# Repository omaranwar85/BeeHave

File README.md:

# BeeHave

This repository contains the board and schematic files (designed in Eagle) for the beehive monitoring system, BeeDAS (Design and development of low-power, long-range data acquisition system for beehives). It also contains a python file 'Script.py' and a numpy file containing the dataset with 1,250 days of beehive sensor data and waether recordings. The sample python script reads the numpy file and uses random forest to estimate the daily weight variations. Following packages are required to run the script.

python                    3.7.11  

pandas                    1.3.2 

matplotlib                3.4.2 

numpy                     1.18.5   

scikit-learn              0.24.2  

seaborn                   0.11.2 

The AllFeatures_shuffled_144.npy file can be downloaded using the folowing link, and should be placed in the same folder as Script.py
https://media.githubusercontent.com/media/omaranwar85/BeeHave/main/AllFeatures_shuffled_144.npy

The datasheets of used components are available online, and can be accessed using the following links

CCS811 Gas Sensor
https://www.sciosense.com/wp-content/uploads/2020/01/SC-001232-DS-2-CCS811B-Datasheet-Revision-2.pdf

SanDisk Industrial
https://images-na.ssl-images-amazon.com/images/I/91tTtUMDM3L.pdf

MMA8452Q Accelerometer
https://www.nxp.com/docs/en/data-sheet/MMA8452Q.pdf

MKR NB-1500 Board
https://store-usa.arduino.cc/products/arduino-mkr-nb-1500

HX711 Load Amplifier
https://datasheetspdf.com/pdf/842201/Aviasemiconductor/HX711/1

BME280 Sensor
https://datasheetspdf.com/pdf/1096951/Bosch/BME280/1

ADMP401 MEMS microphone
https://www.analog.com/media/en/technical-documentation/obsolete-data-sheets/ADMP401.pdf

REF3433 Voltage Reference
https://www.ti.com/lit/ds/symlink/ref3433.pdf

Sparkfun Redboard Turbo
https://www.sparkfun.com/products/14812

As this project progresses, we will be adding more to this repository.

==========================================================================

One of our accepted works at AAAI22 workshop for 'Practical deep-learning in the Wild' also uses the data collected using this system, with a significant overlap with the dataset shared in this repository. You can access this paper using the following link
https://www.researchgate.net/publication/358954859_WE-Bee_Weight_Estimator_for_Beehives_Using_Deep_Learning

If you use this dataset, please refer one of our works.

@inproceedings{anwar2022we,
  title={WE-Bee: Weight Estimator for Beehives Using Deep Learning},
  author={Anwar, Omar and Keating, Adrian and Cardell-Oliver, Rachel and Datta, Amitava and Putrino, Gino},
  booktitle={AAAI Conference on Artificial Intelligence 2022: 1st International Workshop on Practical Deep Learning in the Wild},
  year={2022}
}

@article{anwar2022BeeDAS,
title = {Design and development of low-power, long-range data acquisition system for beehives - BeeDAS},
journal = {Computers and Electronics in Agriculture},
volume = {201},
pages = {107281},
year = {2022},
issn = {0168-1699},
doi = {https://doi.org/10.1016/j.compag.2022.107281},
url = {https://www.sciencedirect.com/science/article/pii/S0168169922005932},
author = {Omar Anwar and Adrian Keating and Rachel Cardell-Oliver and Amitava Datta and Gino Putrino},
keywords = {Data acquisition, Low-power, Long-range, Beehive monitoring, Weight estimation, Random forest},
abstract = {Decision making capability of a system is highly dependent upon the quality and quantity of training data. Majority of beehive monitoring systems developed for research purposes are designed to collect data through a small set of sensors, and from locations with little geographic diversity. This hinders the development of a dataset that can be used to effectively train machine learning models. In this work, we explain the design and development of a multi-sensory, remote data acquisition system for beehives (BeeDAS), with focus on low-power consumption and long-range communication. We address design challenges associated with such systems and highlight the critical issues that need consideration. The proposed system enables collection of data from beehives at remote locations and harsh environment. Results of field deployments elucidate the effectiveness of various sensors which measure temperature, humidity, atmospheric pressure, CO2, acoustics, vibrations and the weight of a hive in hostile environment. This work also uses random forest regression to evaluate the feature importance of different sensors, environmental variables such as temperature, humidity, rain, wind speed as well as the information related to seasons, towards estimating the daily hive weight change, on a dataset comprised of 1,250 days of sensor recordings. We also evaluate the protocol designed for communication using Narrow Band Internet of Things (NB-IoT). The issues related to power optimization, sleep intervals and data storage in remote monitoring are also discussed.}
}

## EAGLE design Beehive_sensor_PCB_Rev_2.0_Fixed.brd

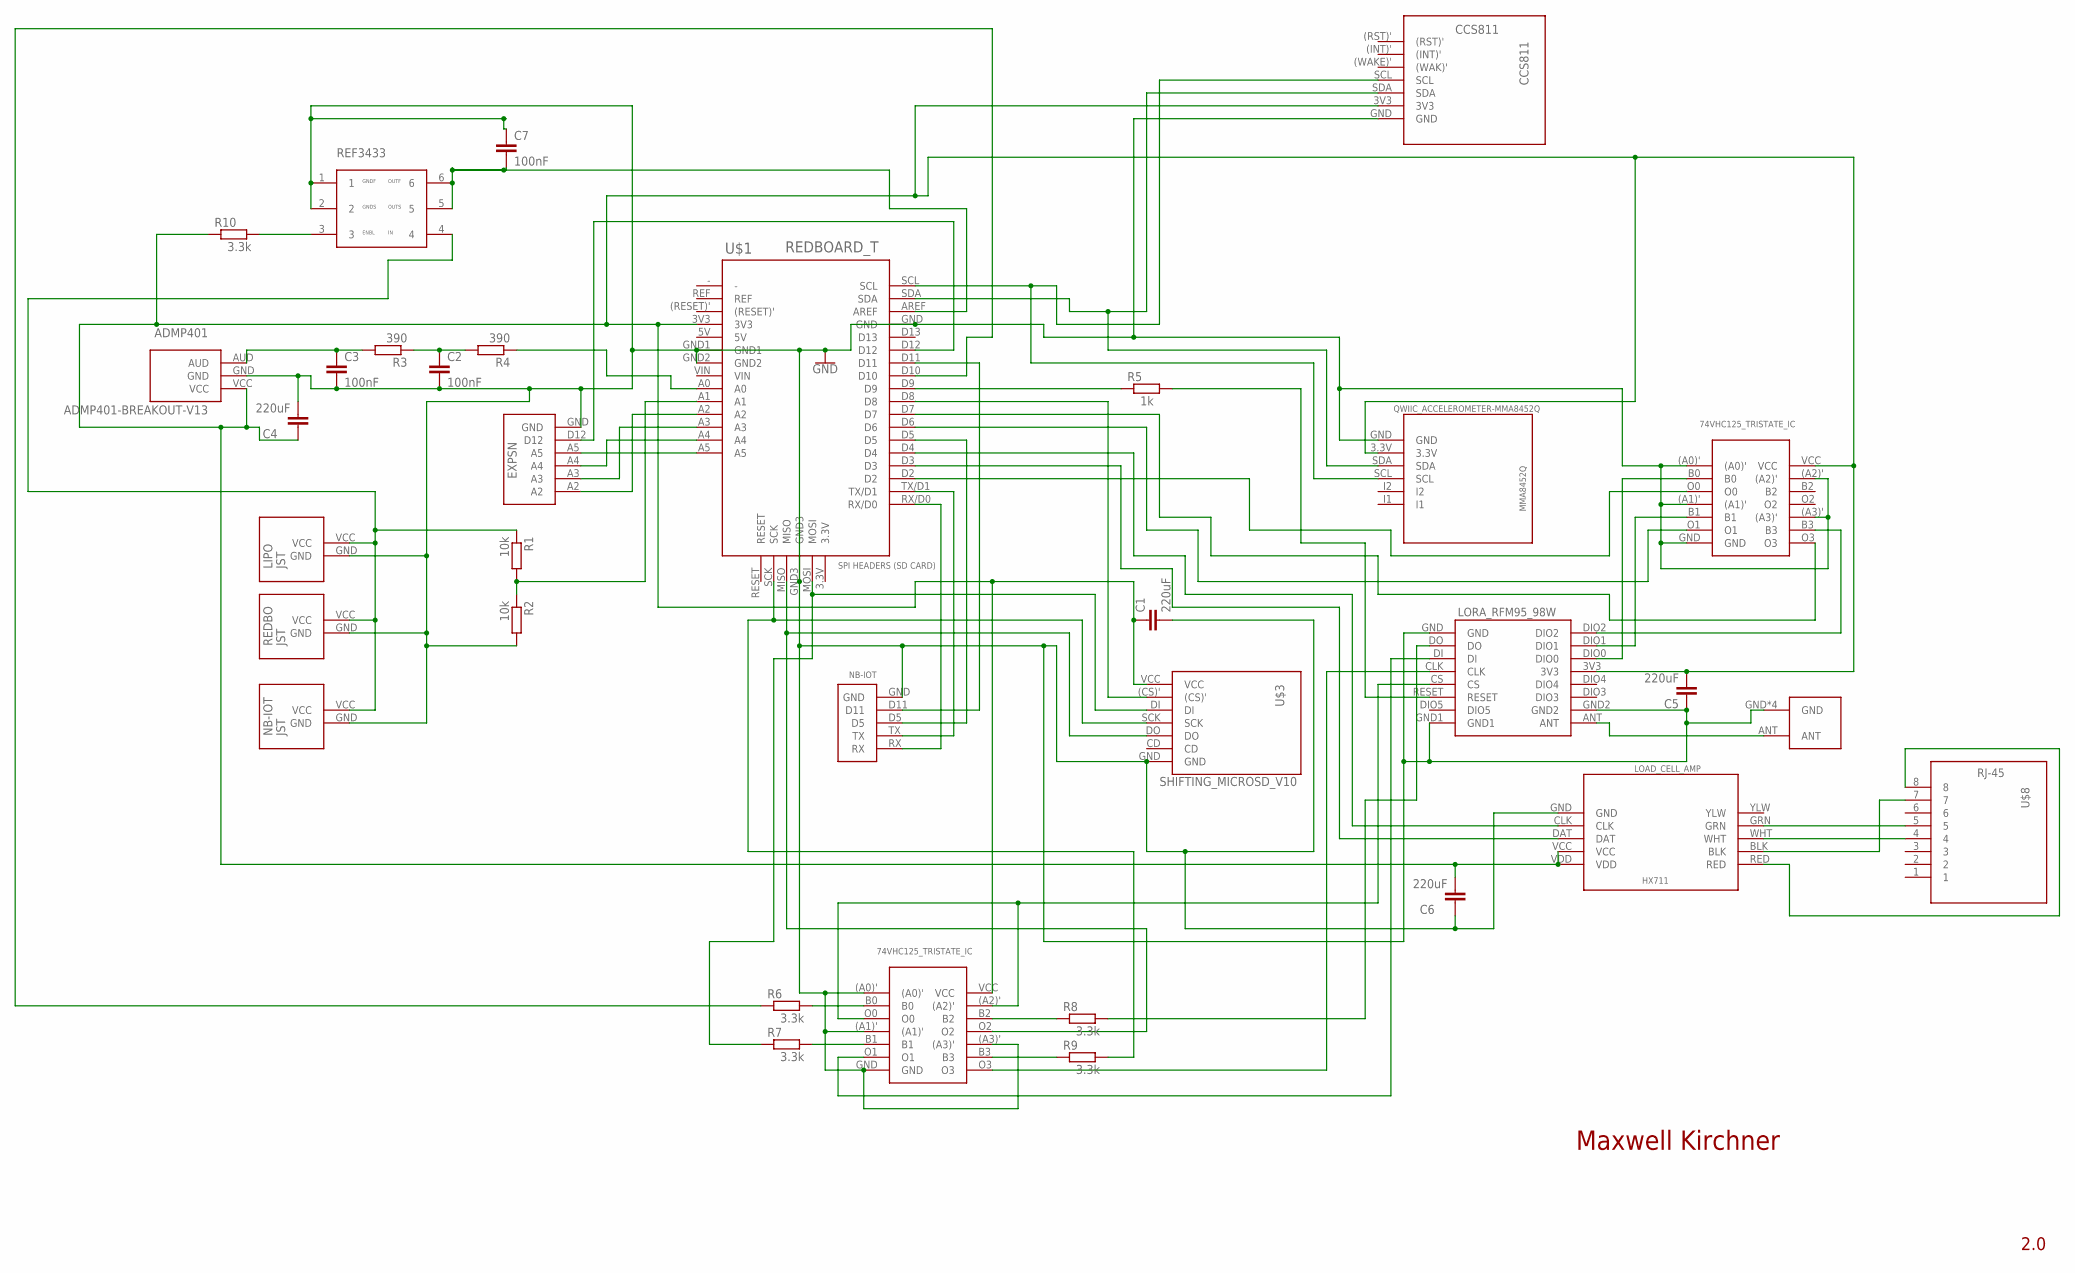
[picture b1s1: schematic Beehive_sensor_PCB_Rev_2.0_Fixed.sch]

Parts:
ADMP401: ADMP401-BREAKOUT-V13
C1, C4, C5, C6: 220uF; C025-025X050
C2, C3: 100nF; C025-025X050
C7: 100nF; C025-024X044
CCS811: CCS811
LIPO: JST
LOAD_CELL_AMP: HX711; HX711_LOAD_CELL_V11
MMA8452Q: QWIIC_ACCELEROMETER-MMA8452Q
NB-IOT: JST
R1, R2: 10k; 0204/7
R3, R4: 390; 0204/7
R5: 1k; 0204/7
R6, R7, R8, R9, R10: 3.3k; 0204/7
REDBO: JST
U$1: REDBOARD_T
U$2: LORA_RFM95_98W; RFM95_98W
U$3: SHIFTING_MICROSD_V10
U$8: RJ-45
U$9, U$14: 74VHC125_TRISTATE_IC; 74VHC125
U$10: ANT
U$11: NB-IOT
U$12: EXPSN
U$13: REF3433

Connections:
GND: ADMP401.GND, C1.2, C2.2, C3.2, C4.2, C5.1, C6.1, C7.1, CCS811.GND, LIPO.GND, LOAD_CELL_AMP.GND, MMA8452Q.GND, NB-IOT.GND, R2.2, REDBO.GND, U$1.GND, U$1.GND1, U$1.GND2, U$1.GND3, U$2.GND, U$2.GND1, U$2.GND2, U$3.GND, U$9.(A0)', U$9.(A1)', U$9.(A3)', U$9.GND, U$10.GND, U$10.GND1 (GND), U$10.GND2 (GND), U$10.GND3 (GND), U$11.GND, U$12.GND, U$13.1, U$13.2, U$14.(A0)', U$14.(A1)', U$14.(A2)', U$14.(A3)', U$14.GND
unnamed: U$1.D8, U$3.(CS)'
unnamed: R7.1, U$1.MOSI, U$3.DI
unnamed: R9.2, U$1.SCK, U$3.SCK
unnamed: U$1.MISO, U$3.DO, U$9.O2
unnamed: CCS811.SCL, MMA8452Q.SCL, U$1.SCL
unnamed: CCS811.SDA, MMA8452Q.SDA, U$1.SDA
unnamed: C7.2, U$1.AREF, U$13.5, U$13.6
unnamed: ADMP401.AUD, C3.1, R3.2
unnamed: R6.2, U$9.B0
unnamed: C2.1, R3.1, R4.2
unnamed: R4.1, U$1.A0
unnamed: U$2.DIO0, U$14.B0
unnamed: LOAD_CELL_AMP.RED, U$8.8
unnamed: LOAD_CELL_AMP.BLK, U$8.7
unnamed: LOAD_CELL_AMP.GRN, U$8.5
unnamed: LOAD_CELL_AMP.WHT, U$8.4
unnamed: LOAD_CELL_AMP.DAT, U$1.D3
unnamed: LOAD_CELL_AMP.CLK, U$1.D4
unnamed: R5.2, U$2.RESET
unnamed: U$2.DIO2, U$14.B3
unnamed: U$2.DIO1, U$14.B1
unnamed: R6.1, U$1.D10
unnamed: LIPO.VCC, NB-IOT.VCC, R1.1, REDBO.VCC, U$13.4
unnamed: U$2.ANT, U$10.ANT
unnamed: R1.2, R2.1, U$1.A1
unnamed: U$1.TX/D1, U$11.TX
unnamed: U$1.RX/D0, U$11.RX
unnamed: U$1.D5, U$11.D5
unnamed: U$1.D11, U$11.D11
unnamed: U$1.A2, U$12.A2
unnamed: U$1.A3, U$12.A3
unnamed: U$1.A4, U$12.A4
unnamed: U$1.A5, U$12.A5
unnamed: U$1.D12, U$12.D12
unnamed: R5.1, U$1.D9
unnamed: U$2.CS, U$9.(A2)', U$9.O0
unnamed: ADMP401.VCC, C1.1, C4.1, C5.2, C6.2, CCS811.3V3, LOAD_CELL_AMP.VCC, LOAD_CELL_AMP.VDD, MMA8452Q.3.3V, R10.1, U$1.3V3, U$2.3V3, U$3.VCC, U$9.VCC, U$14.VCC
unnamed: R7.2, U$9.B1
unnamed: U$2.DI, U$9.O1
unnamed: R8.1, U$9.B2
unnamed: R8.2, U$2.DO
unnamed: R9.1, U$9.B3
unnamed: U$2.CLK, U$9.O3
unnamed: R10.2, U$13.3
unnamed: U$1.D2, U$14.O0
unnamed: U$1.D6, U$14.O1
unnamed: U$1.D7, U$14.O3

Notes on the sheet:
Maxwell Kirchner
2.0

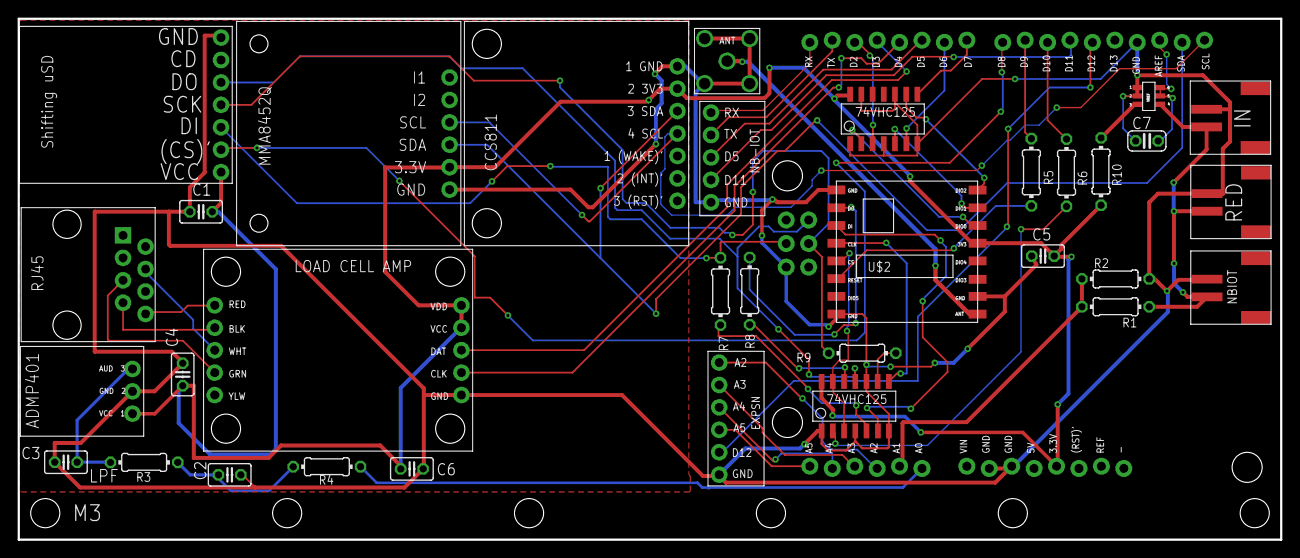
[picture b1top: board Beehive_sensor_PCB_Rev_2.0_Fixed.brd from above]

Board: 2 copper layers, 143.0 x 59.0 mm, 34 parts (1 on the bottom side), 48 nets.

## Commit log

2022-01-11 Add Sensor dataset

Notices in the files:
parts and their libraries:
SparkFun-PowerSymbols: Licensing: Creative Commons ShareAlike 4.0 International - https://creativecommons.org/licenses/by-sa/4.0
